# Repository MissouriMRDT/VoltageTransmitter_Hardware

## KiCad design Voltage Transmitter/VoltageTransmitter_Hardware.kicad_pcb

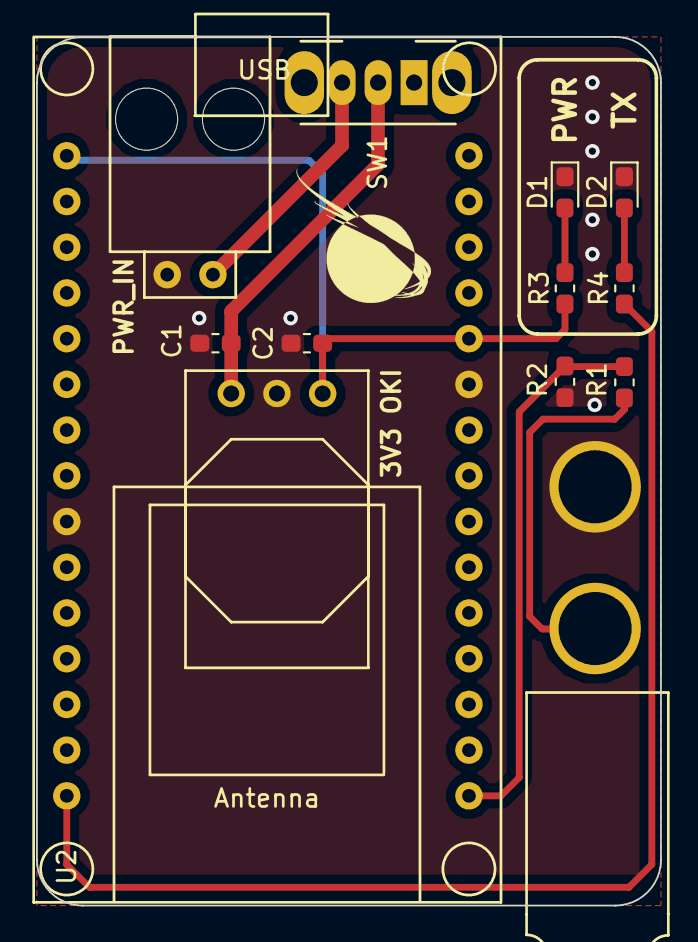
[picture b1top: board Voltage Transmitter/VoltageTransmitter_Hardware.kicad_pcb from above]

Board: 2 copper layers, 34.7 x 48.3 mm, 13 parts (0 on the bottom side), 9 nets.

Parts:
C1, C2: 10uF; C_0603_1608Metric_Pad1.05x0.95mm_HandSolder
Conn1: AndersonPP-MRDT_Connectors; Anderson_2_Horizontal_Stacked
Conn2: Molex_SL_02; MOLEX_SL_02_Horizontal
D1, D2: LED; LED_0603_1608Metric_Pad1.05x0.95mm_HandSolder
R1: 150K; R_0603_1608Metric_Pad1.05x0.95mm_HandSolder
R2: 15K; R_0603_1608Metric_Pad1.05x0.95mm_HandSolder
R3, R4: 500; R_0603_1608Metric_Pad1.05x0.95mm_HandSolder
SW1: SW_Push_SPDT; SW_CuK_OS102011MA1QN1_SPDT_Angled
U1: OKI; OKI_Horizontal
U2: ESP8266_MCU; ESP_8266_NODEMCU

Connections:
+3V3: C2.1, R3.1, U1.3, U2.11, U2.16
Din: R1.2, R2.1, U2.1
GND: C1.2, C2.2, Conn1.2, Conn2.1, D1.1, D2.1, R2.2, U1.2, U2.10, U2.24
unnamed: C1.1, SW1.2, U1.1
unnamed: Conn1.1, R1.1
unnamed: Conn2.2, SW1.3
unnamed: D1.2, R3.2
unnamed: D2.2, R4.2
TX_IND: R4.1, U2.30

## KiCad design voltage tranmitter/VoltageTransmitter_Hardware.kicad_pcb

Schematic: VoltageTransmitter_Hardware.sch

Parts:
C1, C2: 10uF; C_0603_1608Metric_Pad1.05x0.95mm_HandSolder
Conn1: AndersonPP-MRDT_Connectors; Anderson_2_Horisontal_Side_by_Side
Conn2: Molex_SL_02; MOLEX_SL_02_Horizontal
R1: 100K; R_0603_1608Metric_Pad1.05x0.95mm_HandSolder
R2: 11K; R_0603_1608Metric_Pad1.05x0.95mm_HandSolder
U1: OKI; OKI_Horizontal
U2: ESP8266_MCU; ESP_8266 NODEMCU

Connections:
+3V3: C2.1, U1.3, U2.11 (3v3)
Din: R1.2, R2.1, U2.1 (A0)
GND: Conn1.1 (GND), R2.2, U2.10 (GND), U2.24 (GND)
unnamed: C1.1, Conn2.2, U1.1
unnamed: C1.2, C2.2, Conn2.1, U1.2
unnamed: Conn1.2 (V+Log), R1.1

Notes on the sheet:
2 LiPo Batteries
Voltage Divider
Voltage Regulator
ESP8266

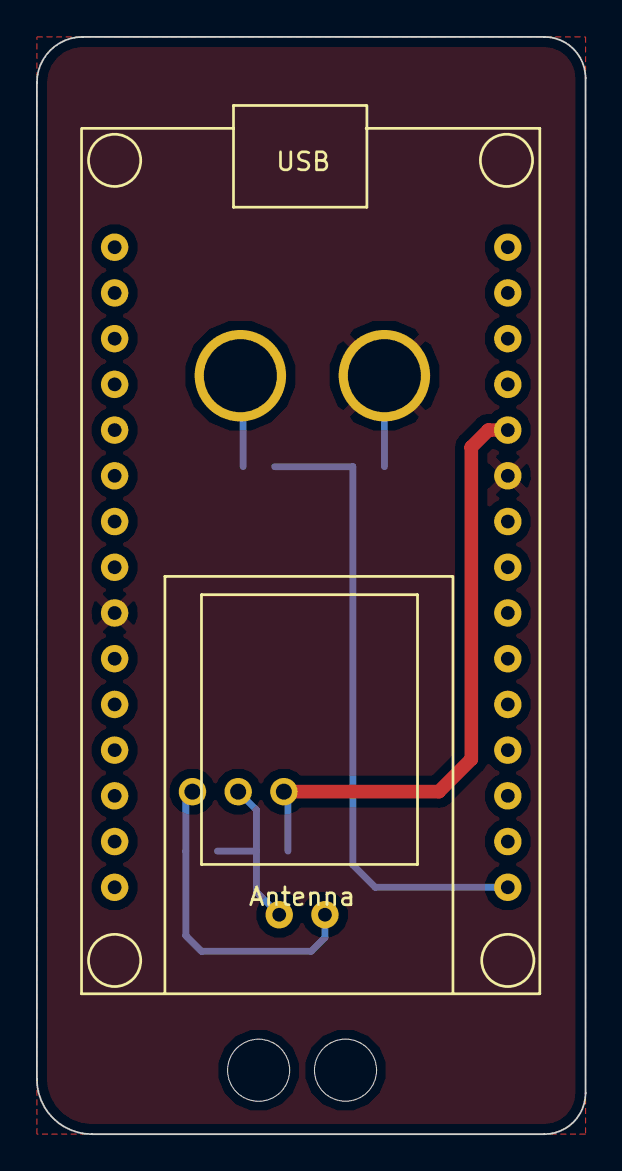
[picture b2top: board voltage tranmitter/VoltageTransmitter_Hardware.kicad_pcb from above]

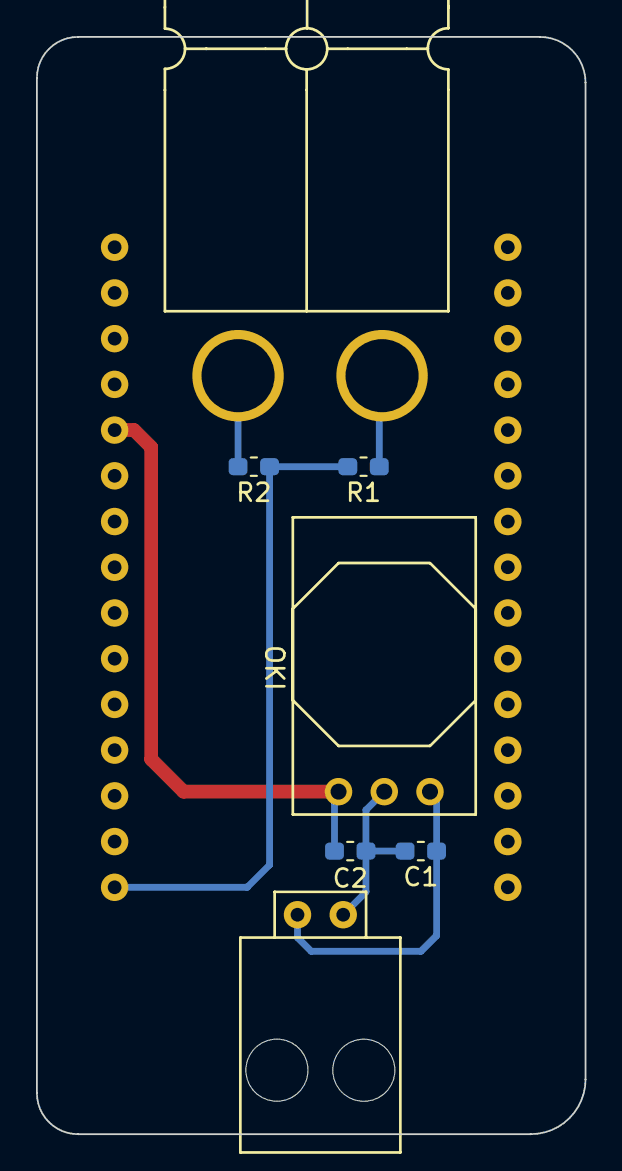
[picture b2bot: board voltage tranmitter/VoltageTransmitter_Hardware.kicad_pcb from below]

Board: 2 copper layers, 30.5 x 61.0 mm, 8 parts (7 on the bottom side), 6 nets.

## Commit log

2018-10-21 PDR work for Voltage Transmitter
    included
    high level block placement
    parts litst minus capcitor and resistors
    schematic of design
2018-10-25 Final PDR Changes
2018-10-25 Final PDR changes 10/25
2018-10-25 hopefully last commit before PDR
2018-12-01 11/30
    fixed some stuff that was important
2018-12-02 CDR stuf
2018-12-03 Changes since First Board Review
2018-12-03 Renamed Files and orgainized a ton
2018-12-03 Voltage Notes
2018-12-07 First Board Review Schematic Changes
2018-12-16 Change the footprint on the ESP8266-added silkscreen
2018-12-16 yeet
2018-12-19 Did the traces for the PCB
2018-12-19 Started BOM
2018-12-19 Finished board
2018-12-19 Added BOM file
2018-12-19 PUSH
2018-12-19 Gerbs Made
2019-03-21 Changed shaped & added comps
    Changed to stacked andersons, added power led, transmitting led, and made sure no comps are located on the bottom of the board.
2019-03-21 Added R2 Gerbs
